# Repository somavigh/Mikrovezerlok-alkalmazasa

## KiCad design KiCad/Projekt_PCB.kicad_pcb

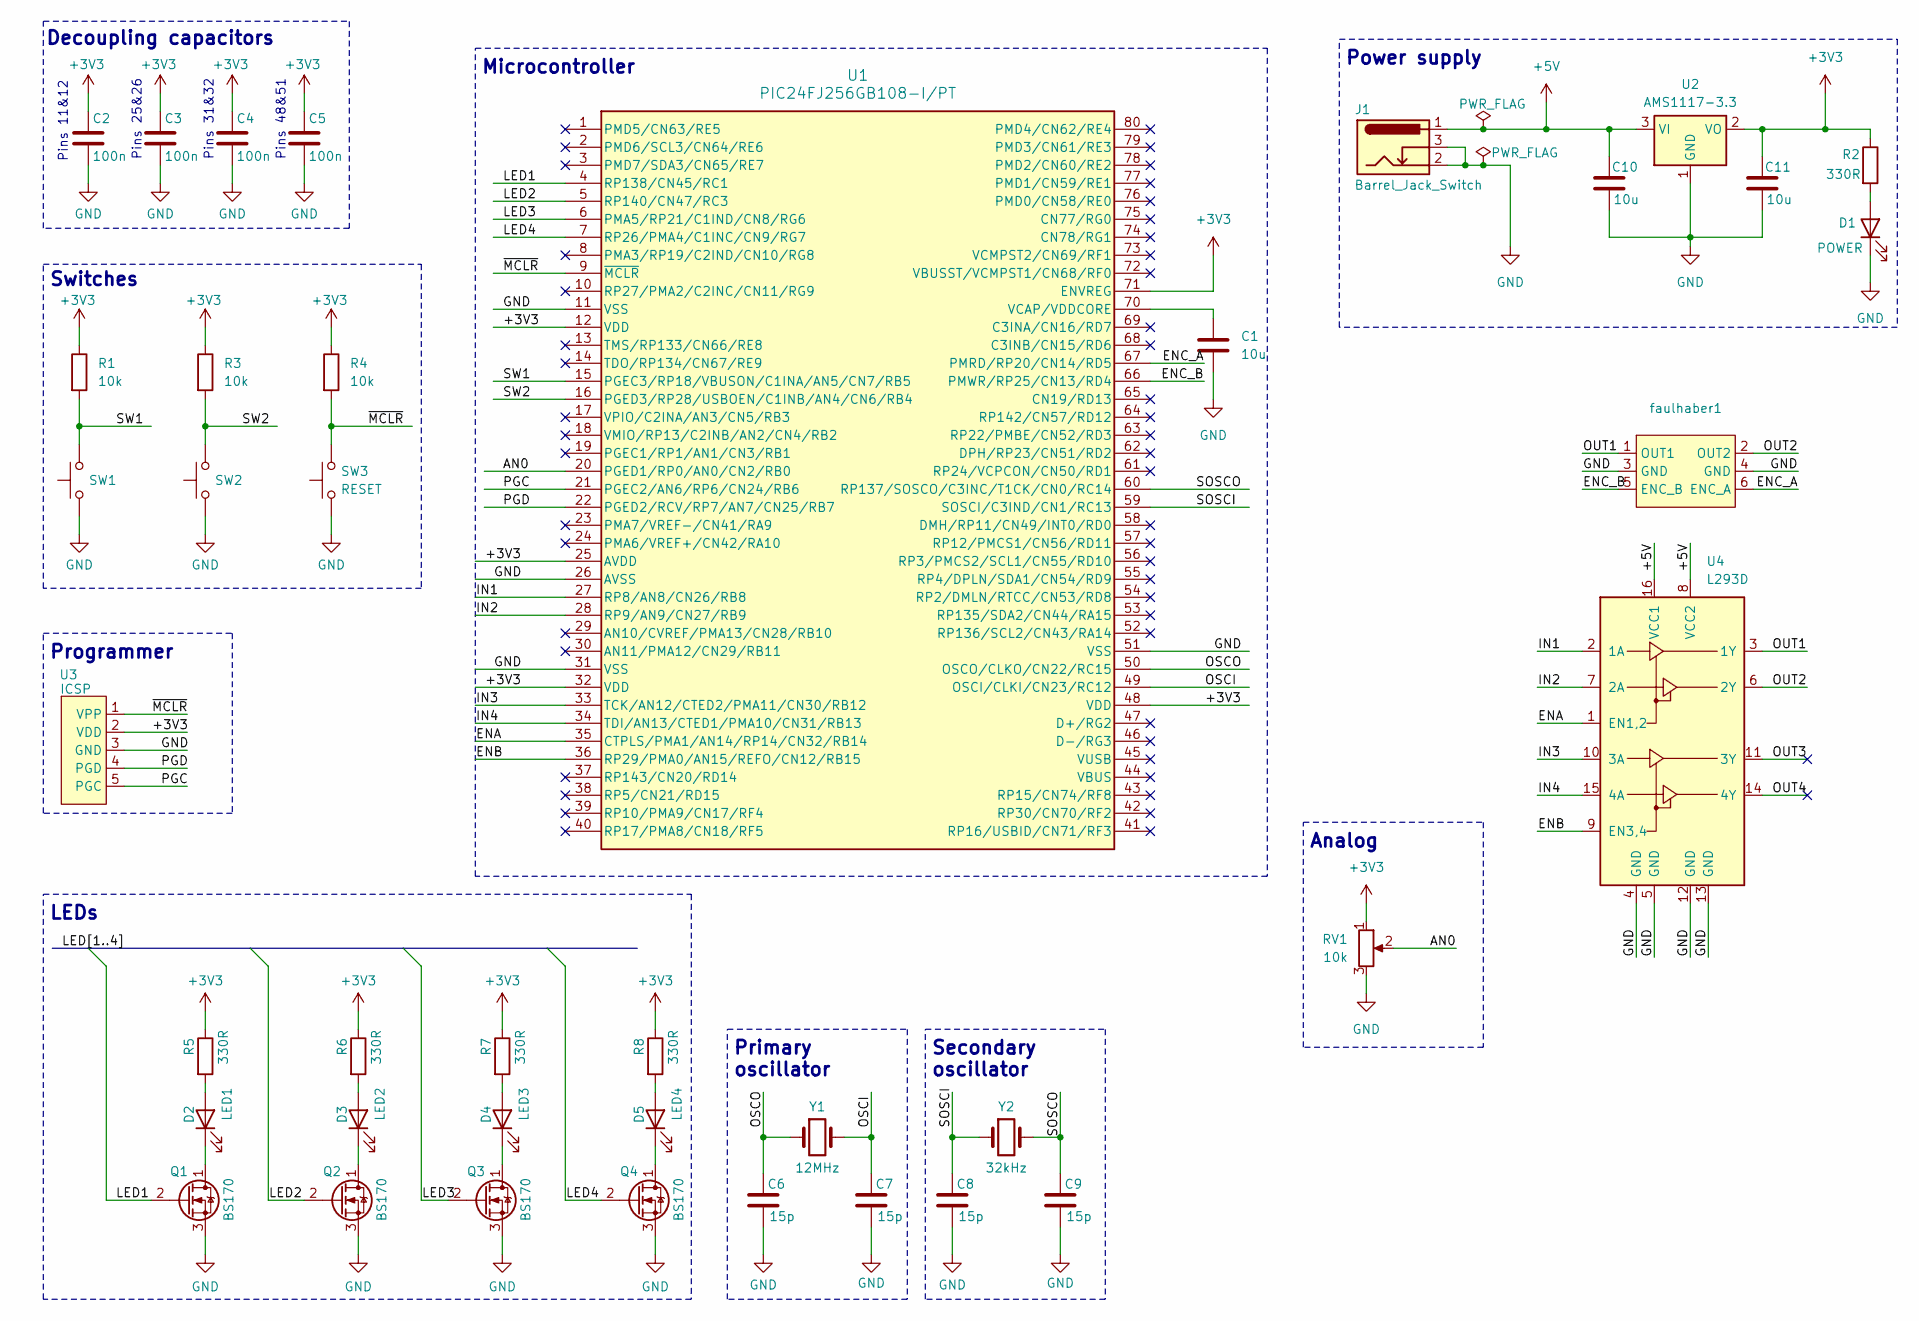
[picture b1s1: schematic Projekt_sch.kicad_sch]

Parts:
C1, C10, C11: 10u; C_1206_3216Metric
C2, C3, C4, C5: 100n; C_0805_2012Metric
C6, C7, C8, C9: 15p; C_0805_2012Metric
D1: POWER; LED_D5.0mm
D2: LED1; LED_D5.0mm
D3: LED2; LED_D5.0mm
D4: LED3; LED_D5.0mm
D5: LED4; LED_D5.0mm
J1: Barrel_Jack_Switch; BarrelJack_Horizontal
Q1, Q2, Q3, Q4: BS170; TO-92_Inline
R1, R3, R4: 10k; R_0805_2012Metric
R2, R5, R6, R7, R8: 330R; R_0805_2012Metric
RV1: 10k; Potentiometer_Bourns_3005_Horizontal
SW1: SW1; SW_PUSH_6mm_H4.3mm
SW2: SW2; SW_PUSH_6mm_H4.3mm
SW3: RESET; SW_PUSH_6mm_H4.3mm
U1: PIC24FJ256GB108-I/PT; TQFP-80_12x12mm_P0.5mm
U2: AMS1117-3.3; SOT-223-3_TabPin2
U3: ICSP
U4: L293D; DIP-16_W7.62mm
Y1: 12MHz; Crystal_HC49-4H_Vertical
Y2: 32kHz; Crystal_C38-LF_D3.0mm_L8.0mm_Horizontal
faulhaber1: PinHeader_2x03_P2.54mm_Vertical_SMD

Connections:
+3V3: C2.1, C3.1, C4.1, C5.1, C11.1, R1.1, R2.1, R3.1, R4.1, R5.1, R6.1, R7.1, R8.1, RV1.1, U1.12 (VDD), U1.25 (AVDD), U1.32 (VDD), U1.48 (VDD), U1.71 (ENVREG), U2.2 (VO), U3.2 (VDD)
+5V: C10.1, J1.1, U2.3 (VI), U4.8 (VCC2), U4.16 (VCC1)
/AN0: RV1.2, U1.20 (PGED1/RP0/AN0/CN2/RB0)
/ENA: U1.35 (CTPLS/PMA1/AN14/RP14/CN32/RB14), U4.1 (EN1,2)
/ENB: U1.36 (RP29/PMA0/AN15/REFO/CN12/RB15), U4.9 (EN3,4)
/ENC_A: U1.67 (PMRD/RP20/CN14/RD5), faulhaber1.6 (ENC_A)
/ENC_B: U1.66 (PMWR/RP25/CN13/RD4), faulhaber1.5 (ENC_B)
/IN1: U1.27 (RP8/AN8/CN26/RB8), U4.2 (1A)
/IN2: U1.28 (RP9/AN9/CN27/RB9), U4.7 (2A)
/IN3: U1.33 (TCK/AN12/CTED2/PMA11/CN30/RB12), U4.10 (3A)
/IN4: U1.34 (TDI/AN13/CTED1/PMA10/CN31/RB13), U4.15 (4A)
/LED1: Q1.2 (G), U1.4 (RP138/CN45/RC1)
/LED2: Q2.2 (G), U1.5 (RP140/CN47/RC3)
/LED3: Q3.2 (G), U1.6 (PMA5/RP21/C1IND/CN8/RG6)
/LED4: Q4.2 (G), U1.7 (RP26/PMA4/C1INC/CN9/RG7)
/OSCI: C7.1, U1.49 (OSCI/CLKI/CN23/RC12), Y1.2
/OSCO: C6.1, U1.50 (OSCO/CLKO/CN22/RC15), Y1.1
/OUT1: U4.3 (1Y), faulhaber1.1 (OUT1)
/OUT2: U4.6 (2Y), faulhaber1.2 (OUT2)
/OUT3: U4.11 (3Y)
/OUT4: U4.14 (4Y)
/PGC: U1.21 (PGEC2/AN6/RP6/CN24/RB6), U3.5 (PGC)
/PGD: U1.22 (PGED2/RCV/RP7/AN7/CN25/RB7), U3.4 (PGD)
/SOSCI: C8.1, U1.59 (SOSCI/C3IND/CN1/RC13), Y2.1
/SOSCO: C9.1, U1.60 (RP137/SOSCO/C3INC/T1CK/CN0/RC14), Y2.2
/SW1: R1.2, SW1.2, U1.15 (PGEC3/RP18/VBUSON/C1INA/AN5/CN7/RB5)
/SW2: R3.2, SW2.2, U1.16 (PGED3/RP28/USBOEN/C1INB/AN4/CN6/RB4)
/~MCLR: R4.2, SW3.2, U1.9 (~MCLR), U3.1 (VPP)
GND: C1.2, C2.2, C3.2, C4.2, C5.2, C6.2, C7.2, C8.2, C9.2, C10.2, C11.2, D1.1 (K), J1.2, J1.3, Q1.3 (S), Q2.3 (S), Q3.3 (S), Q4.3 (S), RV1.3, SW1.1, SW2.1, SW3.1, U1.11 (VSS), U1.26 (AVSS), U1.31 (VSS), U1.51 (VSS), U2.1 (GND), U3.3 (GND), U4.4 (GND), U4.5 (GND), U4.12 (GND), U4.13 (GND), faulhaber1.3 (GND), faulhaber1.4 (GND)
unnamed: D1.2 (A), R2.2
unnamed: D2.2 (A), R5.2
unnamed: D2.1 (K), Q1.1 (D)
unnamed: D3.2 (A), R6.2
unnamed: D3.1 (K), Q2.1 (D)
unnamed: D4.2 (A), R7.2
unnamed: D4.1 (K), Q3.1 (D)
unnamed: D5.2 (A), R8.2
unnamed: D5.1 (K), Q4.1 (D)
unnamed: C1.1, U1.70 (VCAP/VDDCORE)

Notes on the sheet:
Pins 31&32
Pins 11&12
Secondary oscillator
Power supply
Pins 48&51
Primary oscillator
Pins 25&26
Switches
Programmer
Analog
Decoupling capacitors
Microcontroller
LEDs

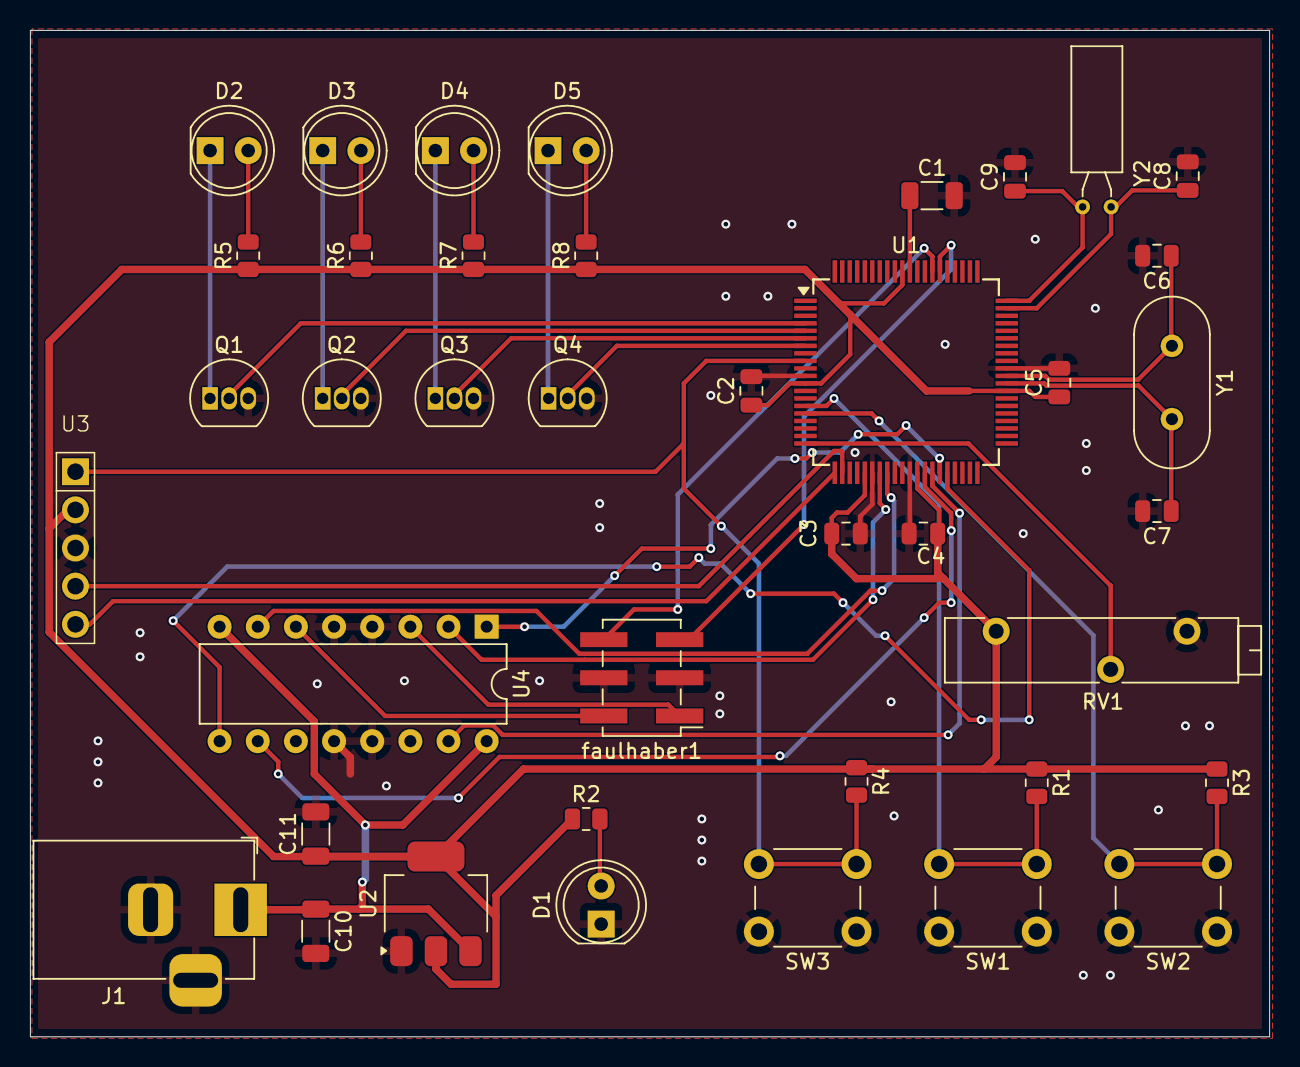
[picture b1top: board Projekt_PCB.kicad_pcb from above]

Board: 2 copper layers, 82.5 x 67.0 mm, 40 parts (0 on the bottom side), 37 nets.

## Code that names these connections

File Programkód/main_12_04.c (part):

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#include <libpic30.h>   // __delay_ms

// LED-ek
#define LED1        _LATG6
#define LED2        _LATG7
#define LED3        _LATG8
#define LED4        _LATG9
#define LEDR        _LATD15
#define LEDG        _LATF4
#define LEDB        _LATF5

// Nyomógombok
#define SW1         !_RC1
#define SW2         !_RC3
#define SW3         !_RE8
#define SW4         !_RE9

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
    // Periféria - láb összerendelés PPS (pp.135)
    __builtin_write_OSCCONL(OSCCON & 0xbf);  //PPSUnLock;
    _RP14R=18; //ENA <- OC1
    __builtin_write_OSCCONL(OSCCON | 0x40); //PPSLock;


    // Lábak iránya
    _TRISG6 = 0; // LED1 kimenet
    _TRISG7 = 0; // LED2 kimenet
    _TRISG8 = 0; // LED3 kimenet
    _TRISG9 = 0; // LED4 kimenet
    _TRISD15 = 0; // LEDR kimenet
    _TRISF4 = 0; // LEDG kimenet
    _TRISF5 = 0; // LEDB kimenet
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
